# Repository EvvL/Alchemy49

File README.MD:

<p align="center">
   
  <br>
  
</p>

**Status:** Ordering final prototype

## Introduction

The Alchemy49 is a replacement pcb for the Magicforce 49 supporting south facing Switches, LEDs, PCB mounted stabilizers
and QMK. It's built around the SparkFun Pro Micro and designed to be easy to put together and solder using only one
surface mount component.

## BOM (Bill of Materials)

- 1x Promicro (or Compatible)
- 1x Micro USB Cable
- 1x XM7D-0512 MiniB (LCSC: C46398)
- 1x 6mm THT SPST Button
- 49x 1N4148 (LCSC: C14538)

If using LEDs:

- 49x 330 1/6w (LCSC: C119858)
- 49x 1.8mm LED (LCSC: C268275)
- 1x AO3402 (LCSC: C351406)
- 1x 100 1/6w (LCSC: C119846)
- 1x 10k 1/6w (LCSC: C119894)

## Layout

Layout Render by [KLE-Render](http://kle-render.herokuapp.com/)

Click [this link](http://www.keyboard-layout-editor.com/#/gists/9abd5a1e1122fe68672f75864f8e92a3) for the KLE layout

## Firmware

For now QMK is currently supported via [KBFirmware.com](https://kbfirmware.com/). Just upload the included
[Configuration/kbfirmware.json](https://github.com/EvvL/Alchemy49/raw/master/Configuration/kbfirmware.json) into
the site, tweak the layout to your liking and compile. The resulting hex file should be flashable using
[AVRDUDESS](https://github.com/zkemble/AVRDUDESS) or [AVRDUDE](http://www.nongnu.org/avrdude/).

If you don't want to adjust anything you can use the [included prebuilt hex file](https://github.com/EvvL/Alchemy49/raw/master/Configuration/alchemy49.hex)
with all the same configuration as the stock MagicForce49 layout.

## Renders

PCB Renders by [Tracespace](https://tracespace.io/view/)

## Copyright and Licensing

This project is licensed under the [Acheron Open-Source Hardware License V1.2](https://github.com/EvvL/Alchemy49/blob/master/LICENSE.md)

OSHWA Certification: [US000215](https://certification.oshwa.org/us000215.html)

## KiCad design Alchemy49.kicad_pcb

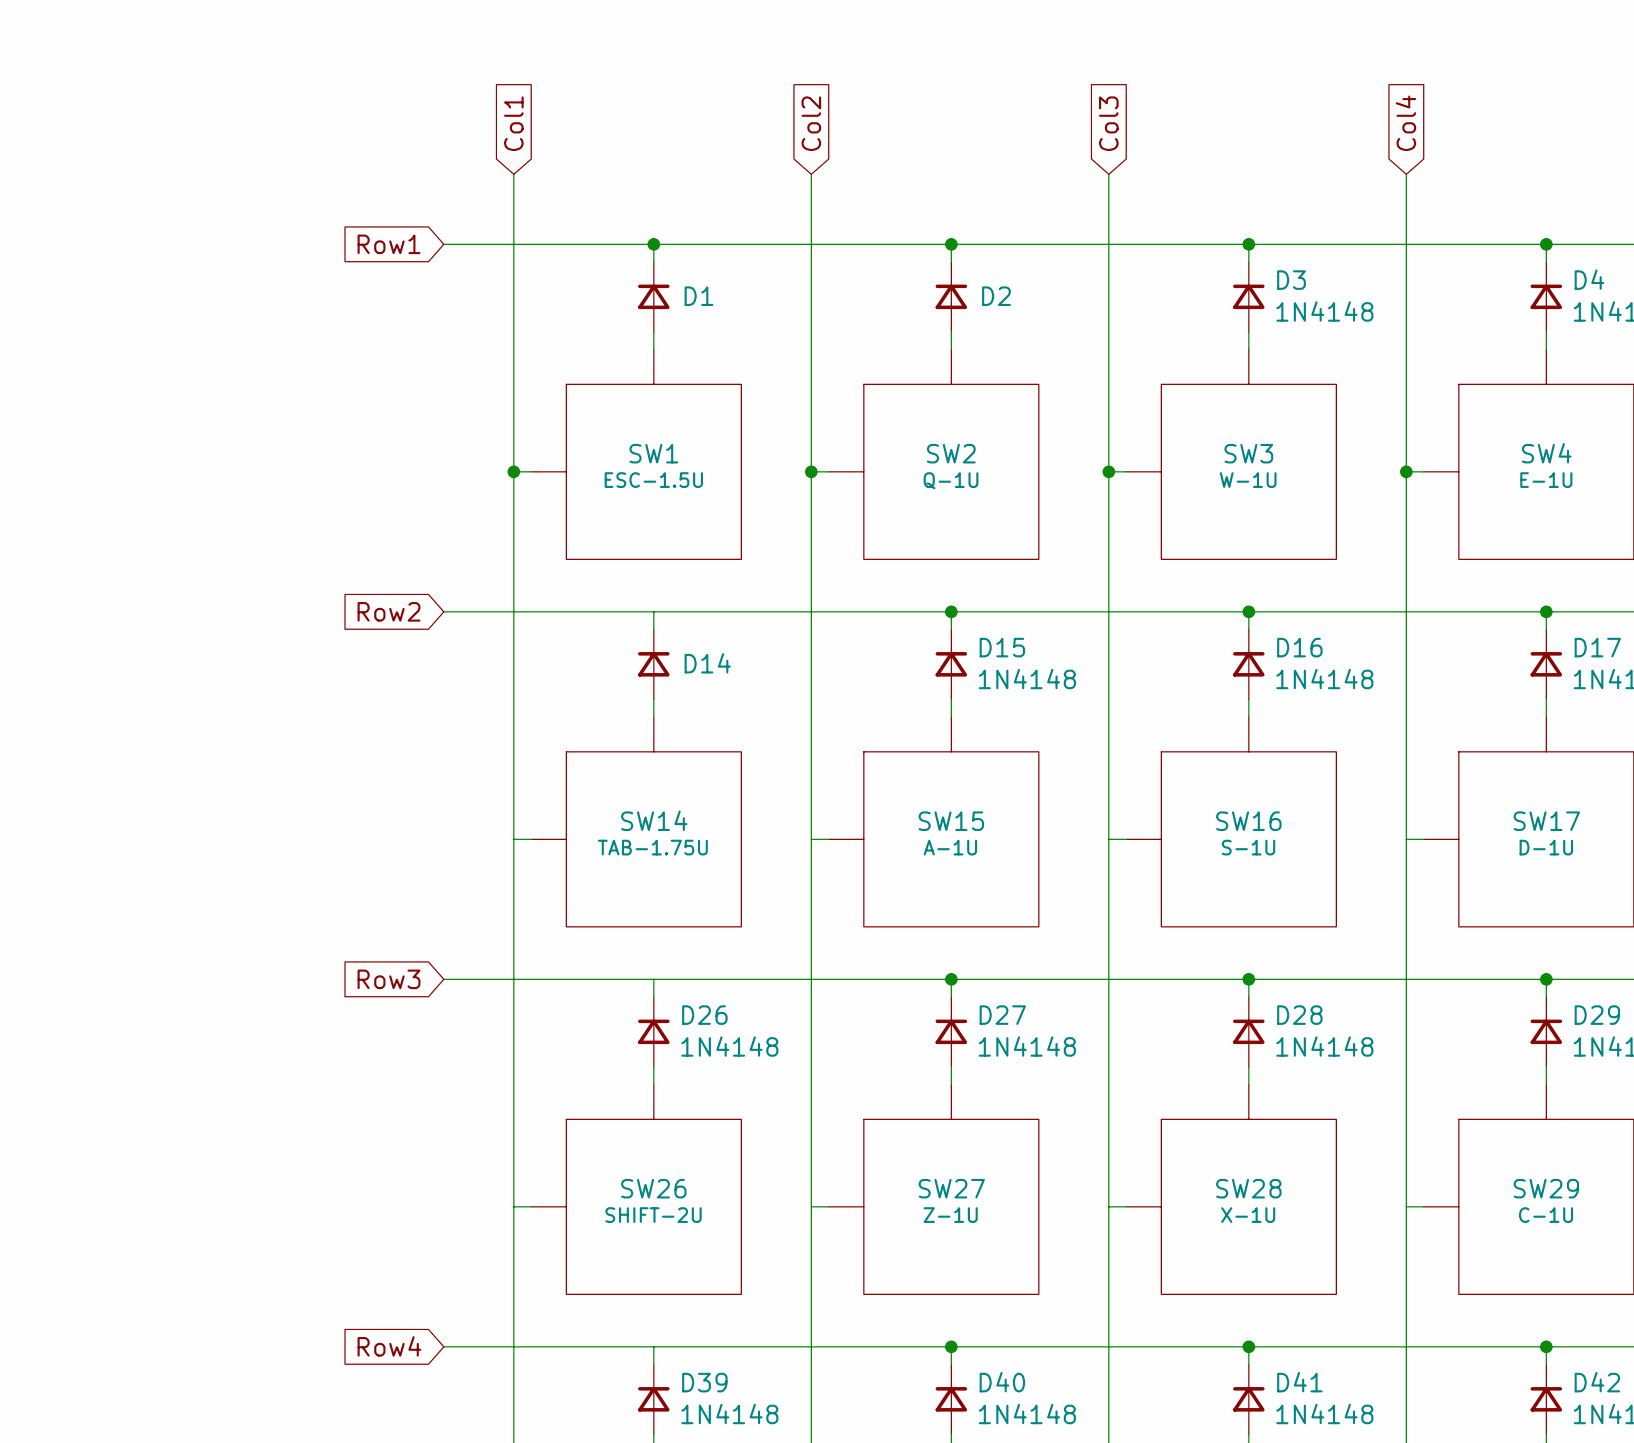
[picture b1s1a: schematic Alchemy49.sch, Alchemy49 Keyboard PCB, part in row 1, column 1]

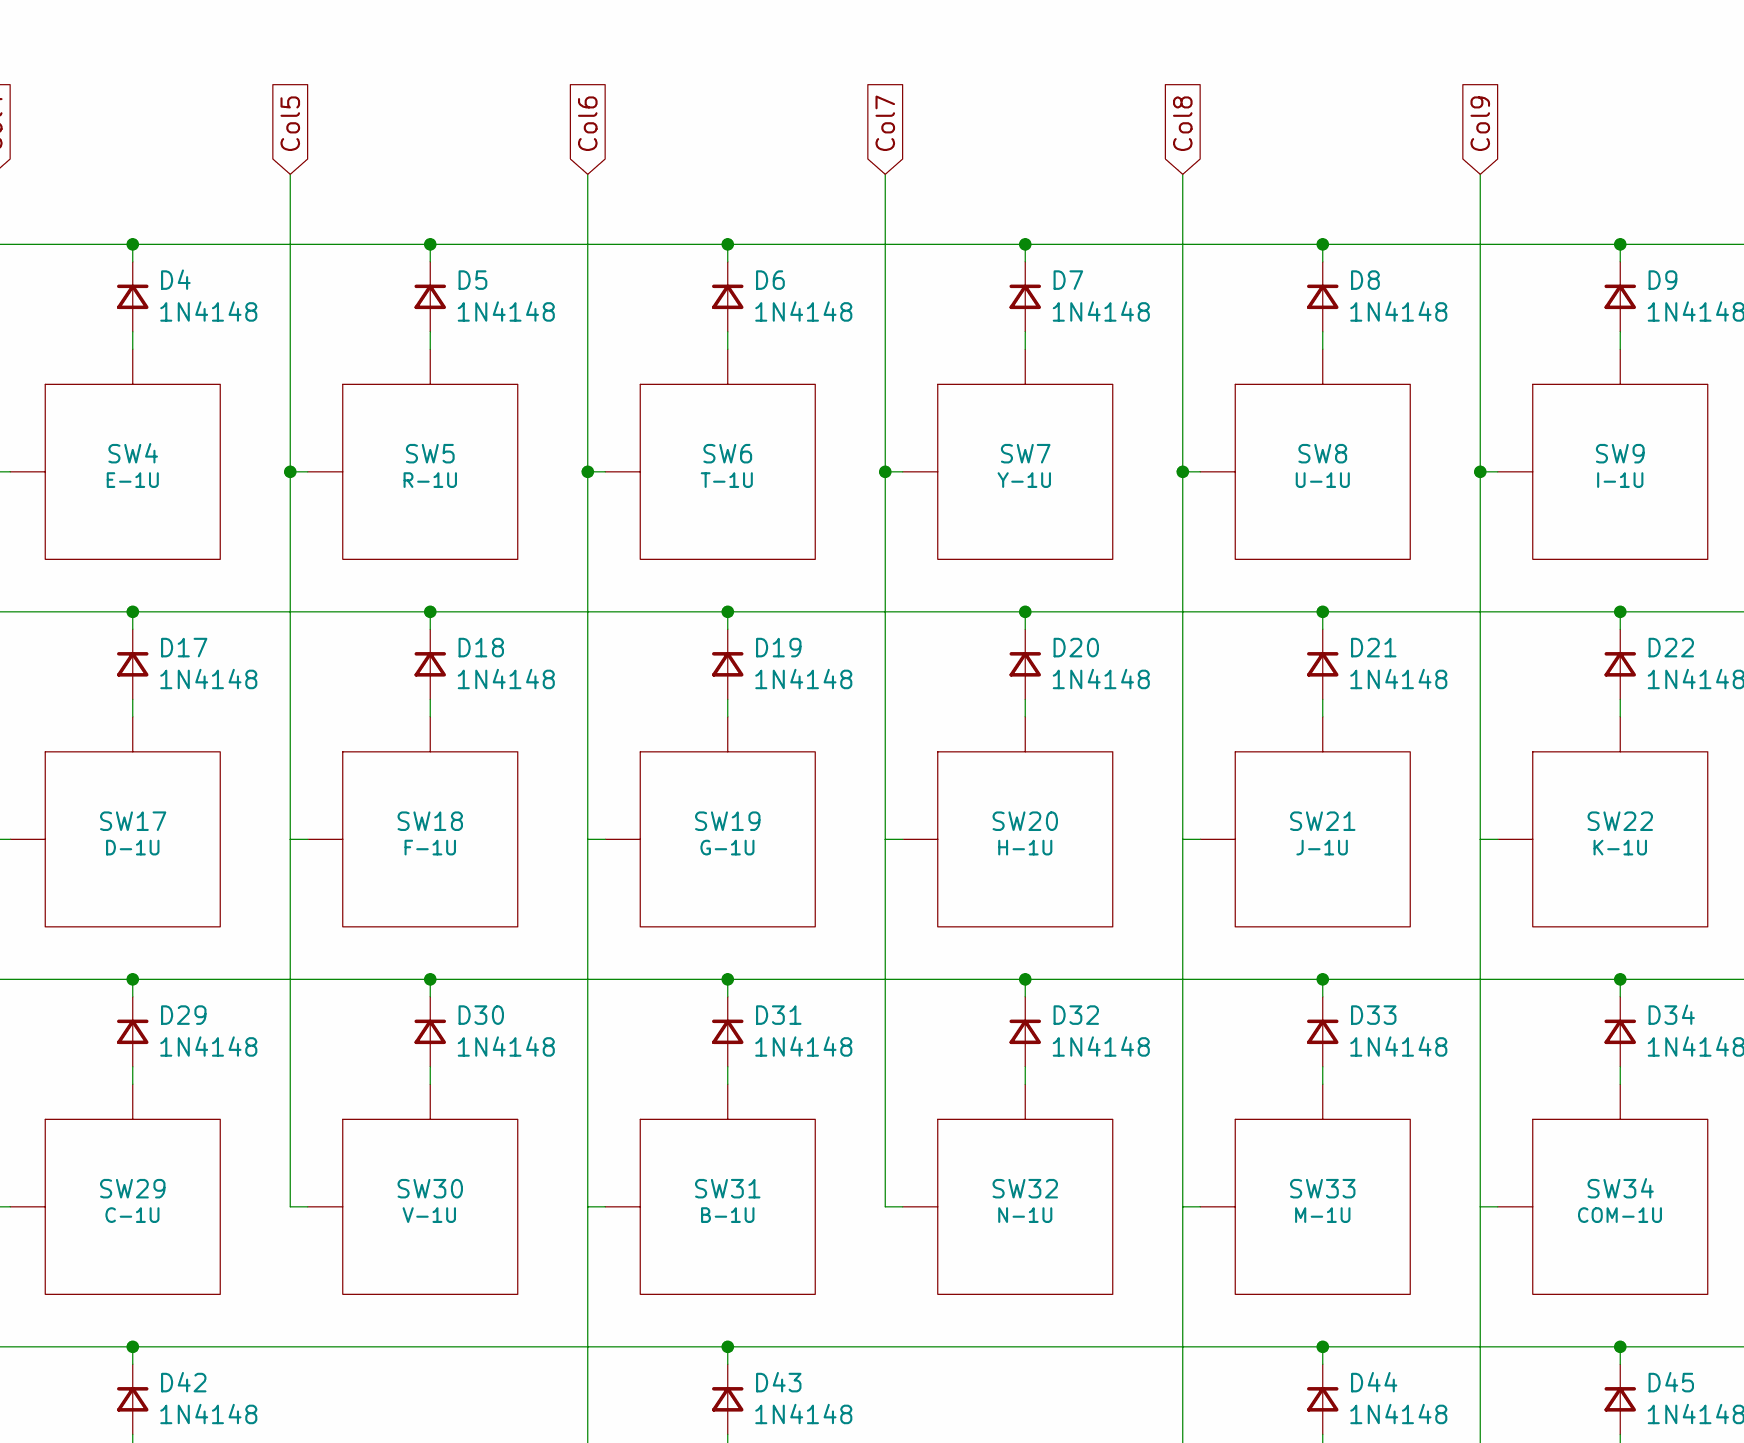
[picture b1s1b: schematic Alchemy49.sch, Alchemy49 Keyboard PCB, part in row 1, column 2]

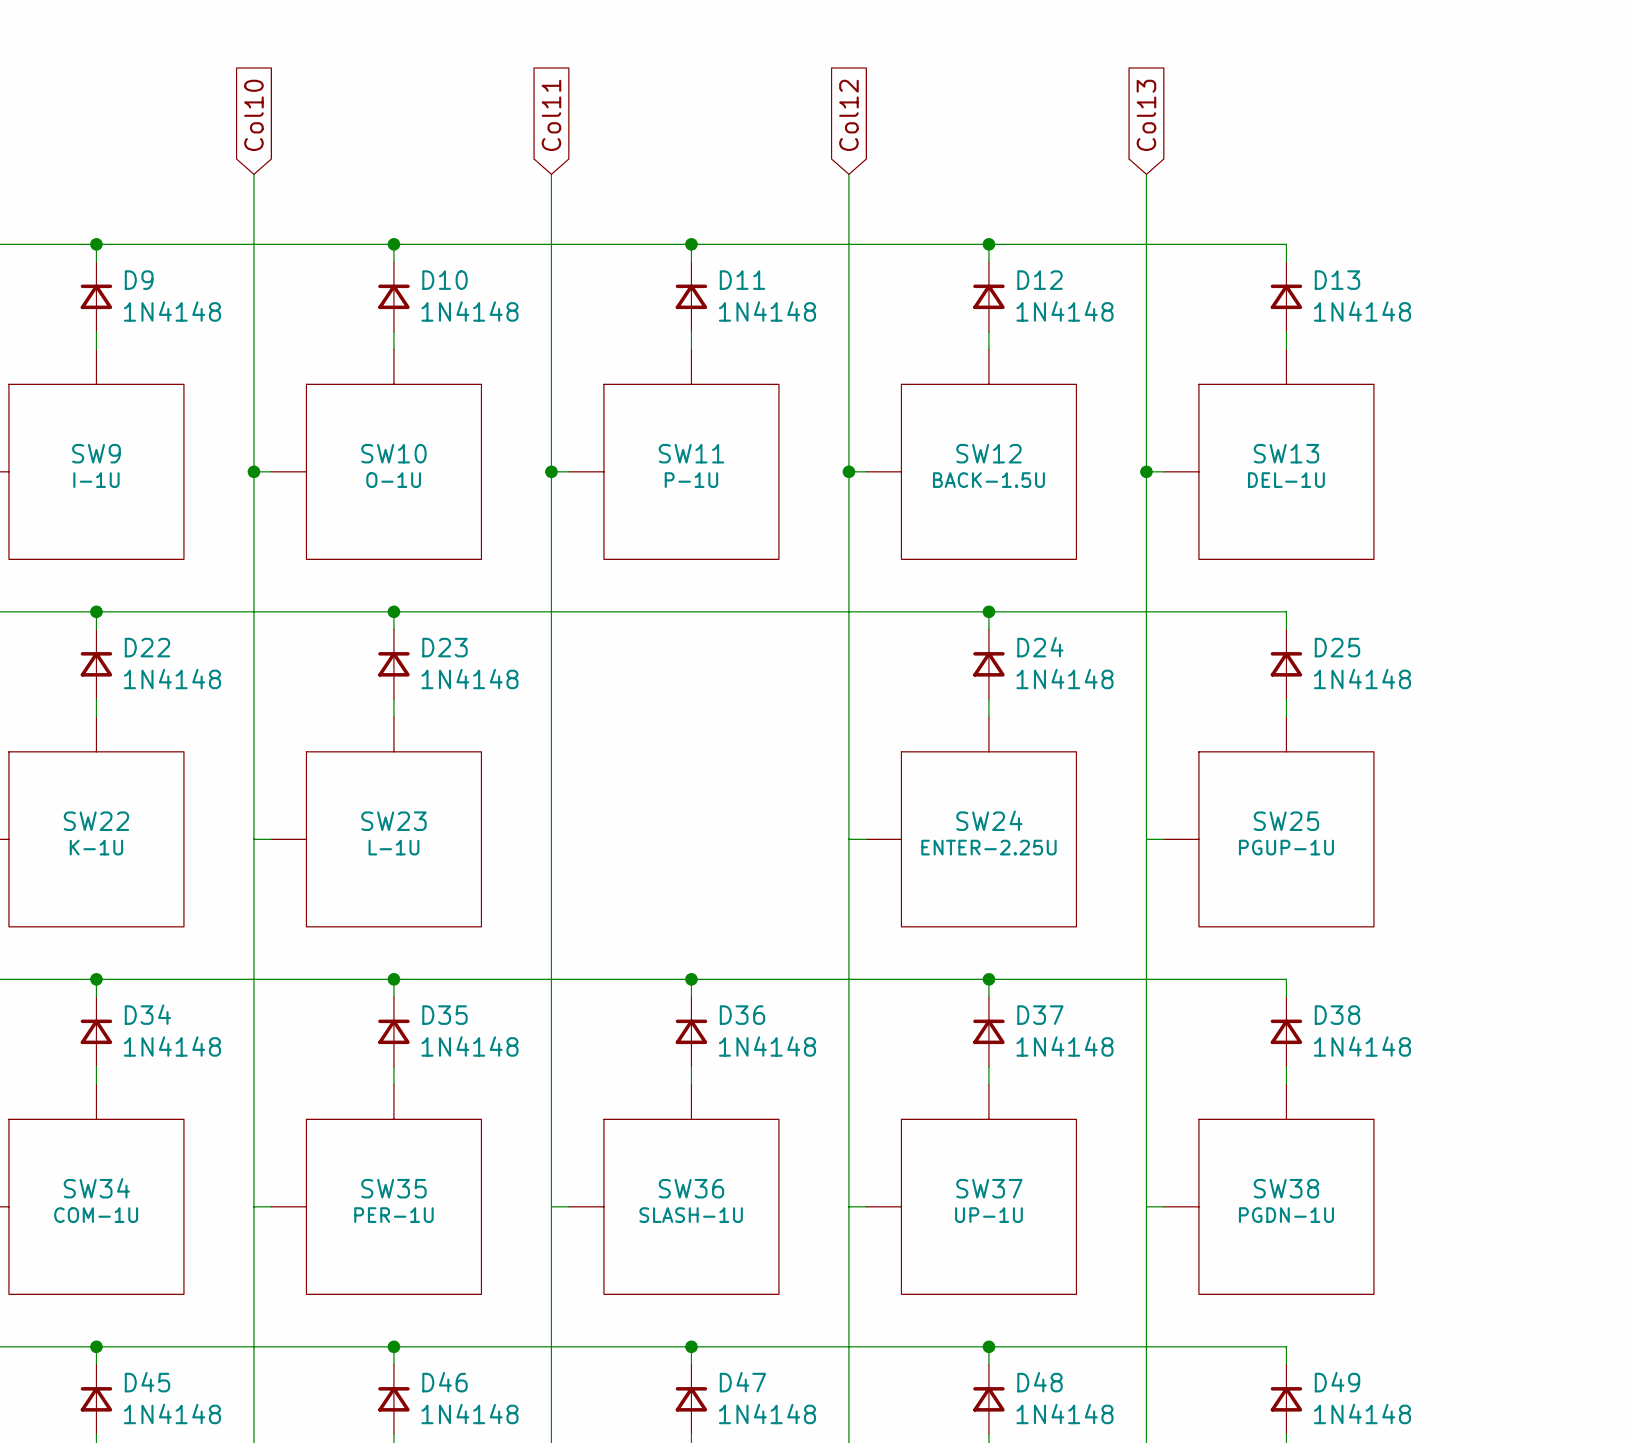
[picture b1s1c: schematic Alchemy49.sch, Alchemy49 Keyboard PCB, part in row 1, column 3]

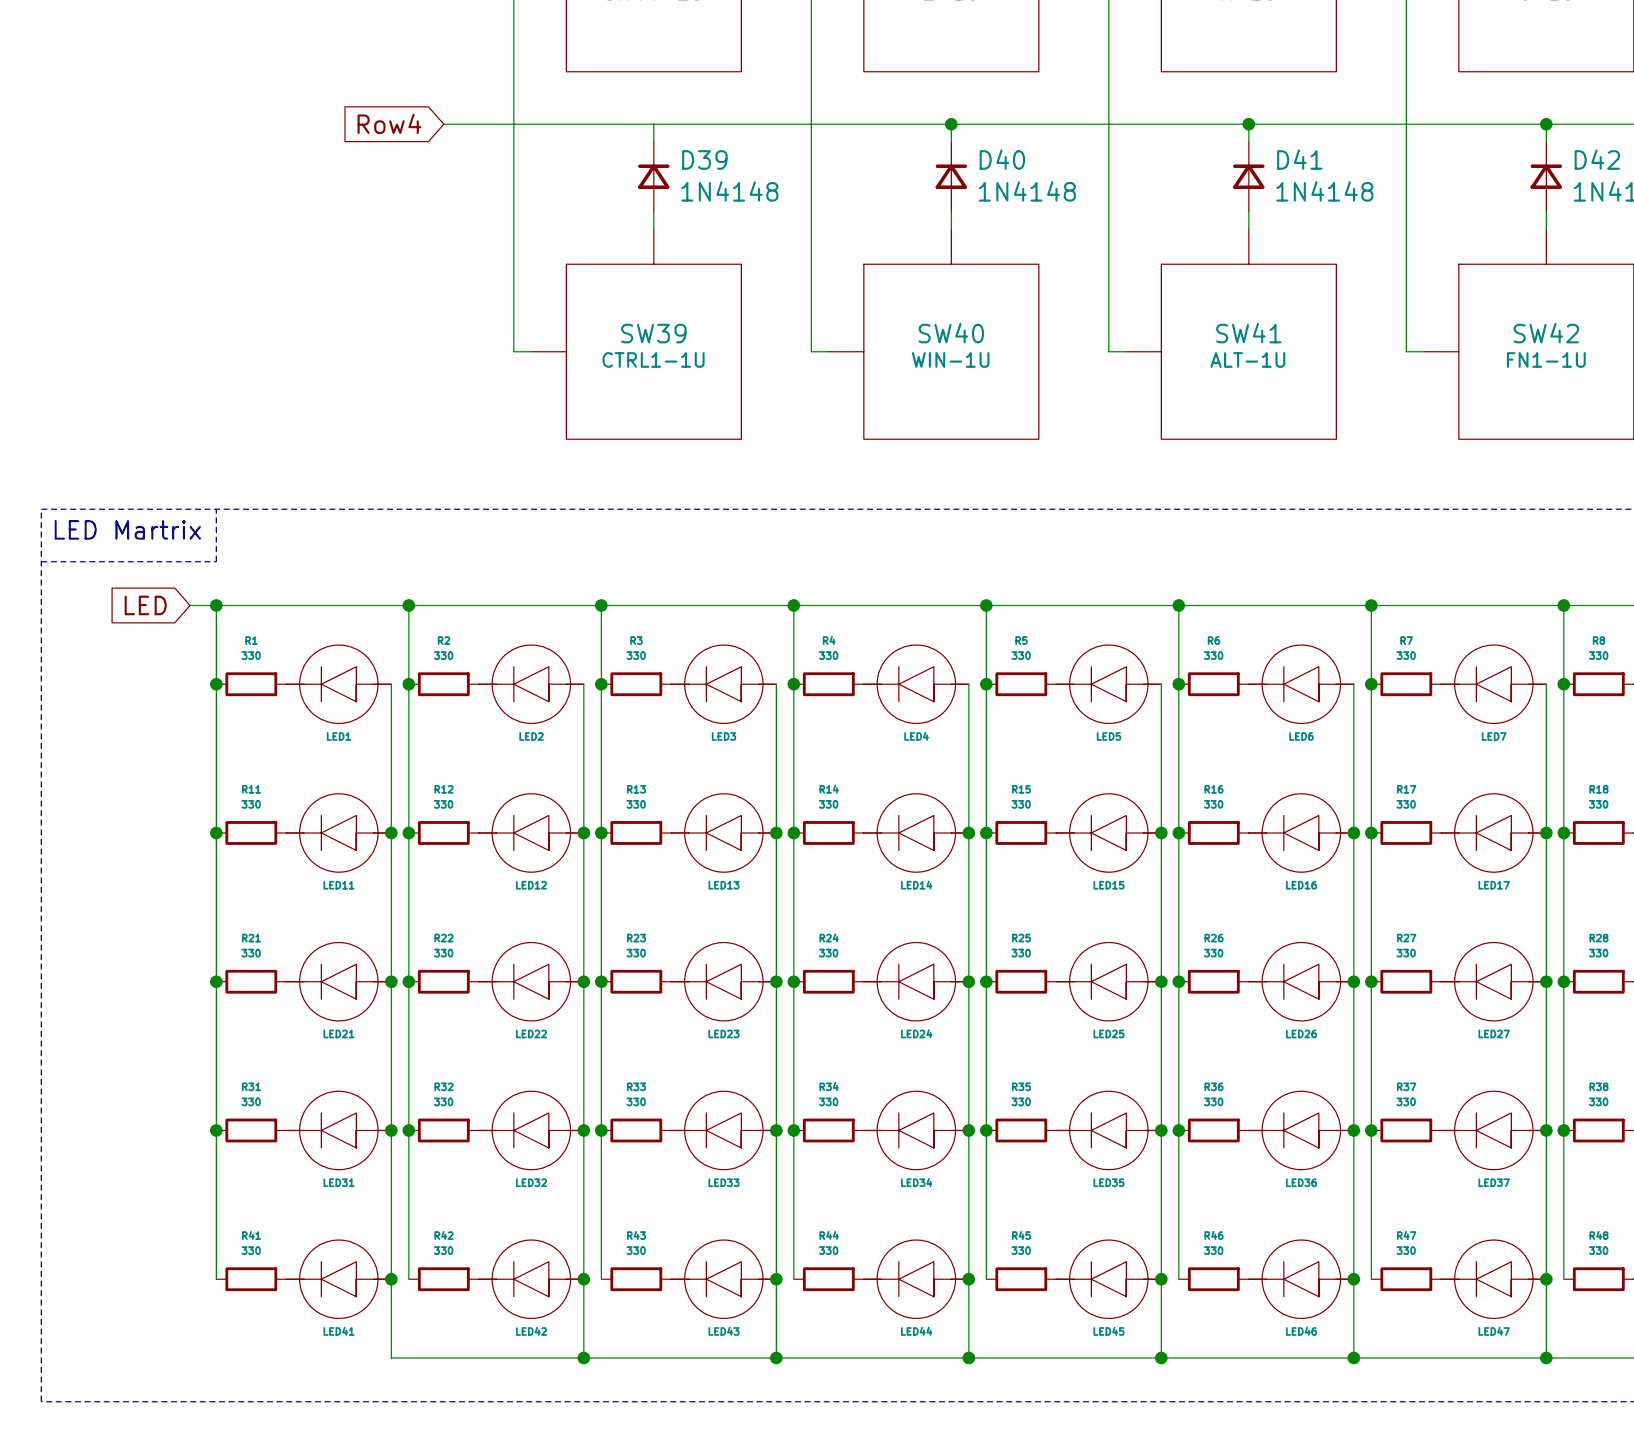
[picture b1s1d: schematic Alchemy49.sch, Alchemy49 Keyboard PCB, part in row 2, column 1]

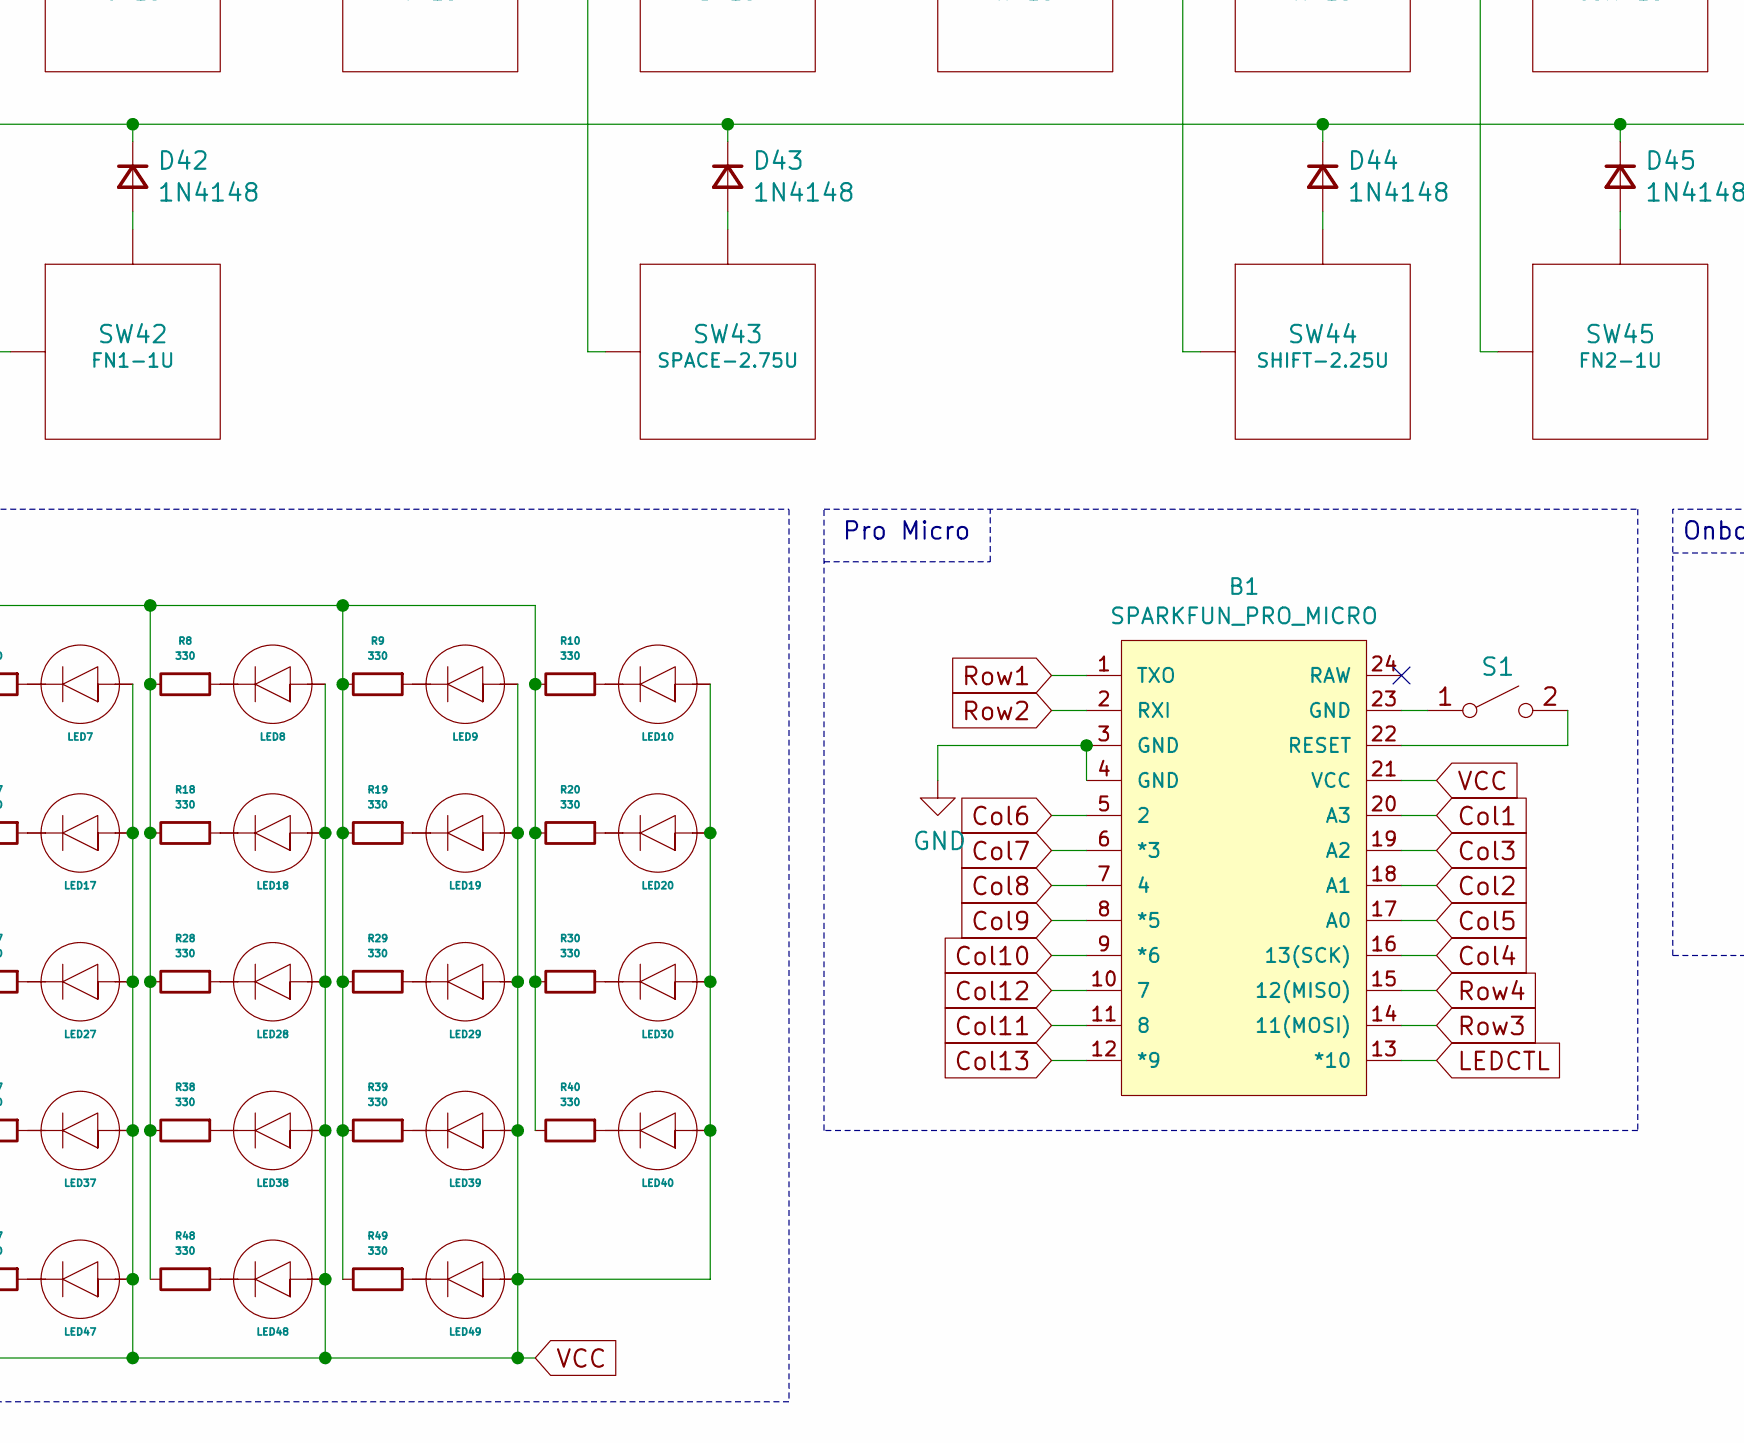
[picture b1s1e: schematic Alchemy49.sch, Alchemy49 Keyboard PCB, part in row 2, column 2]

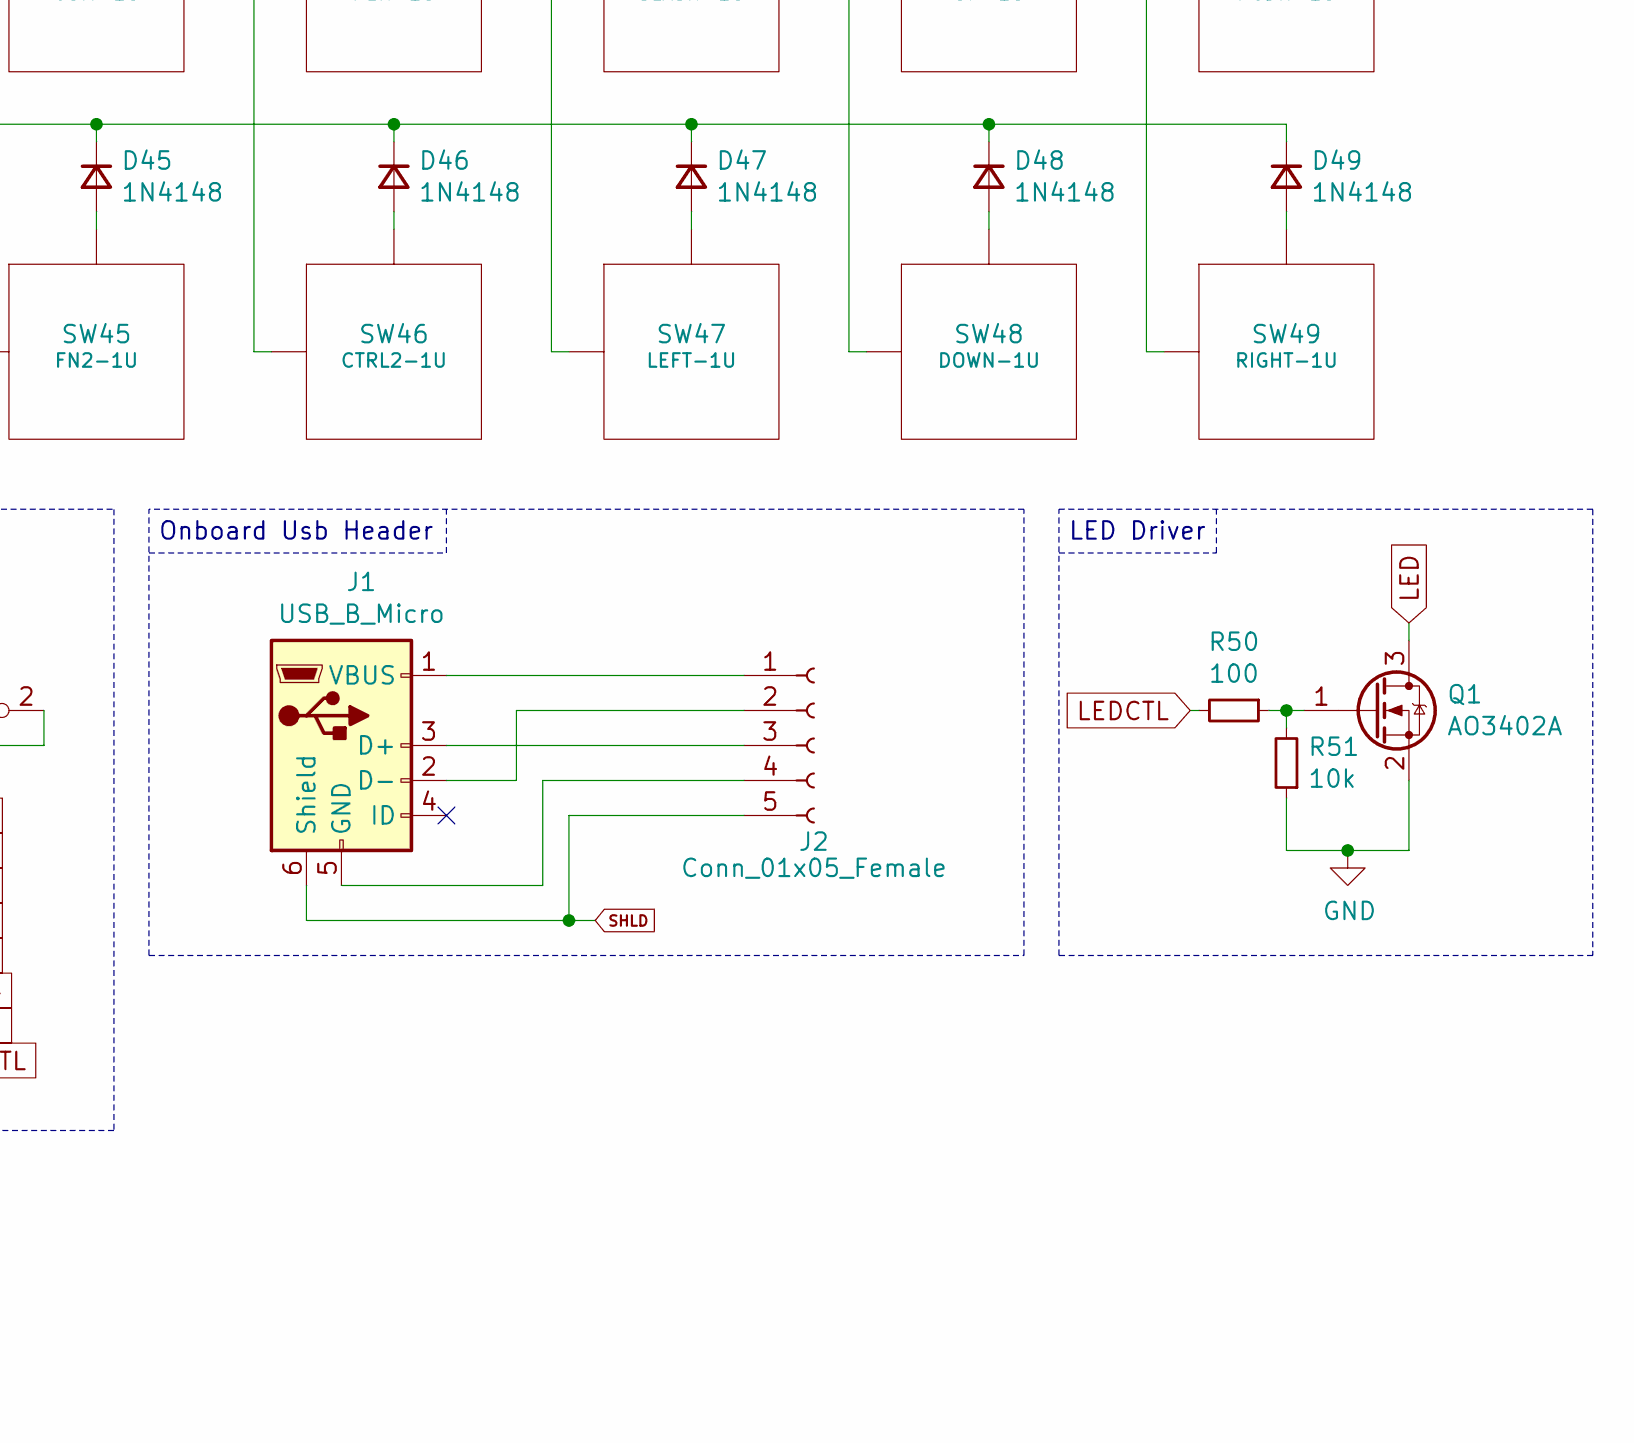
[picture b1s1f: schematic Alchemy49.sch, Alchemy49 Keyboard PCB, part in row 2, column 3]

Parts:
B1: SPARKFUN_PRO_MICRO
D1, D2, D3, D4, D5, D6, D7, D8, D9, D10, D11, D12, D13, D14, D15, D16, D17, D18, D19, D20, D21, D22, D23, D24, D25, D26, D27, D28, D29, D30, D31, D32, D33, D34, D35, D36, D37, D38, D39, D40, D41, D42, D43, D44, D45, D46, D47, D48, D49: 1N4148; D_THT_7.62mm_SOD-123; LCSC C14538
J1: USB_B_Micro; USB_MiniB_XM7D-0512; LCSC C46398
J2: Conn_01x05_Female; PinHeader_1x5_P2.54mm_Vertical
LED1, LED2, LED3, LED4, LED5, LED6, LED7, LED8, LED9, LED10, LED11, LED12, LED13, LED14, LED15, LED16, LED17, LED18, LED19, LED20, LED21, LED22, LED23, LED24, LED25, LED26, LED27, LED28, LED29, LED30, LED31, LED32, LED33, LED34, LED35, LED36, LED37, LED38, LED39, LED40, LED41, LED42, LED43, LED44, LED45, LED46, LED47, LED48, LED49: LED; LED_THT_2.54mm; LCSC C268275
Q1: AO3402A; SOT-23; LCSC C351406
R1, R2, R3, R4, R5, R6, R7, R8, R9, R10, R11, R12, R13, R14, R15, R16, R17, R18, R19, R20, R21, R22, R23, R24, R25, R26, R27, R28, R29, R30, R31, R32, R33, R34, R35, R36, R37, R38, R39, R40, R41, R42, R43, R44, R45, R46, R47, R48, R49: 330; R_THT_5.08mm_SMD_1206; LCSC C119858
R50: 100; R_THT_5.08mm_SMD_1206; LCSC C119846
R51: 10k; R_THT_5.08mm_SMD_1206; LCSC C119894
S1: SW_SPST; SW_PUSH_6mm
SW1: ESC-1.5U; MX150
SW2: Q-1U; MX100
SW3: W-1U; MX100
SW4: E-1U; MX100
SW5: R-1U; MX100
SW6: T-1U; MX100
SW7: Y-1U; MX100
SW8: U-1U; MX100
SW9: I-1U; MX100
SW10: O-1U; MX100
SW11: P-1U; MX100
SW12: BACK-1.5U; MX150
SW13: DEL-1U; MX100
SW14: TAB-1.75U; MX175
SW15: A-1U; MX100
SW16: S-1U; MX100
SW17: D-1U; MX100
SW18: F-1U; MX100
SW19: G-1U; MX100
SW20: H-1U; MX100
SW21: J-1U; MX100
SW22: K-1U; MX100
SW23: L-1U; MX100
SW24: ENTER-2.25U; MX225
SW25: PGUP-1U; MX100
SW26: SHIFT-2U; MX200
SW27: Z-1U; MX100
SW28: X-1U; MX100
SW29: C-1U; MX100
SW30: V-1U; MX100
SW31: B-1U; MX100
SW32: N-1U; MX100
SW33: M-1U; MX100
SW34: COM-1U; MX100
SW35: PER-1U; MX100
SW36: SLASH-1U; MX100
SW37: UP-1U; MX100
SW38: PGDN-1U; MX100
SW39: CTRL1-1U; MX100
SW40: WIN-1U; MX100
SW41: ALT-1U; MX100
SW42: FN1-1U; MX100
SW43: SPACE-2.75U; MX275R
SW44: SHIFT-2.25U; MX225R
SW45: FN2-1U; MX100
SW46: CTRL2-1U; MX100
SW47: LEFT-1U; MX100
SW48: DOWN-1U; MX100
SW49: RIGHT-1U; MX100

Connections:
Col1: B1.20 (A3), SW1.1 (Col), SW14.1 (Col), SW26.1 (Col), SW39.1 (Col)
Col2: B1.18 (A1), SW2.1 (Col), SW15.1 (Col), SW27.1 (Col), SW40.1 (Col)
Col3: B1.19 (A2), SW3.1 (Col), SW16.1 (Col), SW28.1 (Col), SW41.1 (Col)
Col4: B1.16 (13(SCK)), SW4.1 (Col), SW17.1 (Col), SW29.1 (Col), SW42.1 (Col)
Col5: B1.17 (A0), SW5.1 (Col), SW18.1 (Col), SW30.1 (Col)
Col6: B1.5 (2), SW6.1 (Col), SW19.1 (Col), SW31.1 (Col), SW43.1 (Col)
Col7: B1.6 (*3), SW7.1 (Col), SW20.1 (Col), SW32.1 (Col)
Col8: B1.7 (4), SW8.1 (Col), SW21.1 (Col), SW33.1 (Col), SW44.1 (Col)
Col9: B1.8 (*5), SW9.1 (Col), SW22.1 (Col), SW34.1 (Col), SW45.1 (Col)
Col10: B1.9 (*6), SW10.1 (Col), SW23.1 (Col), SW35.1 (Col), SW46.1 (Col)
Col11: B1.11 (8), SW11.1 (Col), SW36.1 (Col), SW47.1 (Col)
Col12: B1.10 (7), SW12.1 (Col), SW24.1 (Col), SW37.1 (Col), SW48.1 (Col)
Col13: B1.12 (*9), SW13.1 (Col), SW25.1 (Col), SW38.1 (Col), SW49.1 (Col)
GND: B1.3 (GND), B1.4 (GND), Q1.2 (S), R51.1
LED: Q1.3 (D), R1.2, R2.2, R3.2, R4.2, R5.2, R6.2, R7.2, R8.2, R9.2, R10.2, R11.2, R12.2, R13.2, R14.2, R15.2, R16.2, R17.2, R18.2, R19.2, R20.2, R21.2, R22.2, R23.2, R24.2, R25.2, R26.2, R27.2, R28.2, R29.2, R30.2, R31.2, R32.2, R33.2, R34.2, R35.2, R36.2, R37.2, R38.2, R39.2, R40.2, R41.2, R42.2, R43.2, R44.2, R45.2, R46.2, R47.2, R48.2, R49.2
LEDCTL: B1.13 (*10), R50.2
unnamed: B1.22 (RESET), S1.2 (B)
unnamed: B1.23 (GND), S1.1 (A)
unnamed: D1.2 (A), SW1.2 (Row)
unnamed: D2.2 (A), SW2.2 (Row)
unnamed: D3.2 (A), SW3.2 (Row)
unnamed: D4.2 (A), SW4.2 (Row)
unnamed: D5.2 (A), SW5.2 (Row)
unnamed: D6.2 (A), SW6.2 (Row)
unnamed: D7.2 (A), SW7.2 (Row)
unnamed: D8.2 (A), SW8.2 (Row)
unnamed: D9.2 (A), SW9.2 (Row)
unnamed: D10.2 (A), SW10.2 (Row)
unnamed: D11.2 (A), SW11.2 (Row)
unnamed: D12.2 (A), SW12.2 (Row)
unnamed: D13.2 (A), SW13.2 (Row)
unnamed: D14.2 (A), SW14.2 (Row)
unnamed: D15.2 (A), SW15.2 (Row)
unnamed: D16.2 (A), SW16.2 (Row)
unnamed: D17.2 (A), SW17.2 (Row)
unnamed: D18.2 (A), SW18.2 (Row)
unnamed: D19.2 (A), SW19.2 (Row)
unnamed: D20.2 (A), SW20.2 (Row)
unnamed: D21.2 (A), SW21.2 (Row)
unnamed: D22.2 (A), SW22.2 (Row)
unnamed: D23.2 (A), SW23.2 (Row)
unnamed: D24.2 (A), SW24.2 (Row)
unnamed: D25.2 (A), SW25.2 (Row)
unnamed: D26.2 (A), SW26.2 (Row)
unnamed: D27.2 (A), SW27.2 (Row)
unnamed: D28.2 (A), SW28.2 (Row)
unnamed: D29.2 (A), SW29.2 (Row)
unnamed: D30.2 (A), SW30.2 (Row)
unnamed: D31.2 (A), SW31.2 (Row)
unnamed: D32.2 (A), SW32.2 (Row)
unnamed: D33.2 (A), SW33.2 (Row)
unnamed: D34.2 (A), SW34.2 (Row)
unnamed: D35.2 (A), SW35.2 (Row)
unnamed: D36.2 (A), SW36.2 (Row)
unnamed: D37.2 (A), SW37.2 (Row)
unnamed: D38.2 (A), SW38.2 (Row)
unnamed: D39.2 (A), SW39.2 (Row)
unnamed: D40.2 (A), SW40.2 (Row)
unnamed: D41.2 (A), SW41.2 (Row)
unnamed: D42.2 (A), SW42.2 (Row)
unnamed: D43.2 (A), SW43.2 (Row)
unnamed: D44.2 (A), SW44.2 (Row)
unnamed: D45.2 (A), SW45.2 (Row)
unnamed: D46.2 (A), SW46.2 (Row)
unnamed: D47.2 (A), SW47.2 (Row)
unnamed: D48.2 (A), SW48.2 (Row)
unnamed: D49.2 (A), SW49.2 (Row)
unnamed: J1.1 (VBUS), J2.1
unnamed: J1.2 (D-), J2.2
unnamed: J1.3 (D+), J2.3
unnamed: J1.5 (GND), J2.4
unnamed: LED1.K, R1.1
unnamed: LED2.K, R2.1
unnamed: LED3.K, R3.1
unnamed: LED4.K, R4.1
unnamed: LED5.K, R5.1
unnamed: LED6.K, R6.1
unnamed: LED7.K, R7.1
unnamed: LED8.K, R8.1
unnamed: LED9.K, R9.1
unnamed: LED10.K, R10.1
unnamed: LED11.K, R11.1
unnamed: LED12.K, R12.1
unnamed: LED13.K, R13.1
unnamed: LED14.K, R14.1
unnamed: LED15.K, R15.1
unnamed: LED16.K, R16.1
unnamed: LED17.K, R17.1
unnamed: LED18.K, R18.1
unnamed: LED19.K, R19.1
unnamed: LED20.K, R20.1
unnamed: LED21.K, R21.1
unnamed: LED22.K, R22.1
unnamed: LED23.K, R23.1
unnamed: LED24.K, R24.1
unnamed: LED25.K, R25.1
unnamed: LED26.K, R26.1
unnamed: LED27.K, R27.1
unnamed: LED28.K, R28.1
unnamed: LED29.K, R29.1
unnamed: LED30.K, R30.1
unnamed: LED31.K, R31.1
unnamed: LED32.K, R32.1
unnamed: LED33.K, R33.1
unnamed: LED34.K, R34.1
unnamed: LED35.K, R35.1
unnamed: LED36.K, R36.1
unnamed: LED37.K, R37.1
unnamed: LED38.K, R38.1
unnamed: LED39.K, R39.1
unnamed: LED40.K, R40.1
unnamed: LED41.K, R41.1
unnamed: LED42.K, R42.1
unnamed: LED43.K, R43.1
unnamed: LED44.K, R44.1
unnamed: LED45.K, R45.1
unnamed: LED46.K, R46.1
unnamed: LED47.K, R47.1
unnamed: LED48.K, R48.1
unnamed: LED49.K, R49.1
unnamed: Q1.1 (G), R50.1, R51.2
Row1: B1.1 (TXO), D1.1 (K), D2.1 (K), D3.1 (K), D4.1 (K), D5.1 (K), D6.1 (K), D7.1 (K), D8.1 (K), D9.1 (K), D10.1 (K), D11.1 (K), D12.1 (K), D13.1 (K)
Row2: B1.2 (RXI), D14.1 (K), D15.1 (K), D16.1 (K), D17.1 (K), D18.1 (K), D19.1 (K), D20.1 (K), D21.1 (K), D22.1 (K), D23.1 (K), D24.1 (K), D25.1 (K)
Row3: B1.14 (11(MOSI)), D26.1 (K), D27.1 (K), D28.1 (K), D29.1 (K), D30.1 (K), D31.1 (K), D32.1 (K), D33.1 (K), D34.1 (K), D35.1 (K), D36.1 (K), D37.1 (K), D38.1 (K)
Row4: B1.15 (12(MISO)), D39.1 (K), D40.1 (K), D41.1 (K), D42.1 (K), D43.1 (K), D44.1 (K), D45.1 (K), D46.1 (K), D47.1 (K), D48.1 (K), D49.1 (K)
SHLD: J1.6 (Shield), J2.5
VCC: B1.21 (VCC), LED1.A, LED2.A, LED3.A, LED4.A, LED5.A, LED6.A, LED7.A, LED8.A, LED9.A, LED10.A, LED11.A, LED12.A, LED13.A, LED14.A, LED15.A, LED16.A, LED17.A, LED18.A, LED19.A, LED20.A, LED21.A, LED22.A, LED23.A, LED24.A, LED25.A, LED26.A, LED27.A, LED28.A, LED29.A, LED30.A, LED31.A, LED32.A, LED33.A, LED34.A, LED35.A, LED36.A, LED37.A, LED38.A, LED39.A, LED40.A, LED41.A, LED42.A, LED43.A, LED44.A, LED45.A, LED46.A, LED47.A, LED48.A, LED49.A

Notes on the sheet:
Onboard Usb Header
Pro Micro
LED Martrix
LED Driver

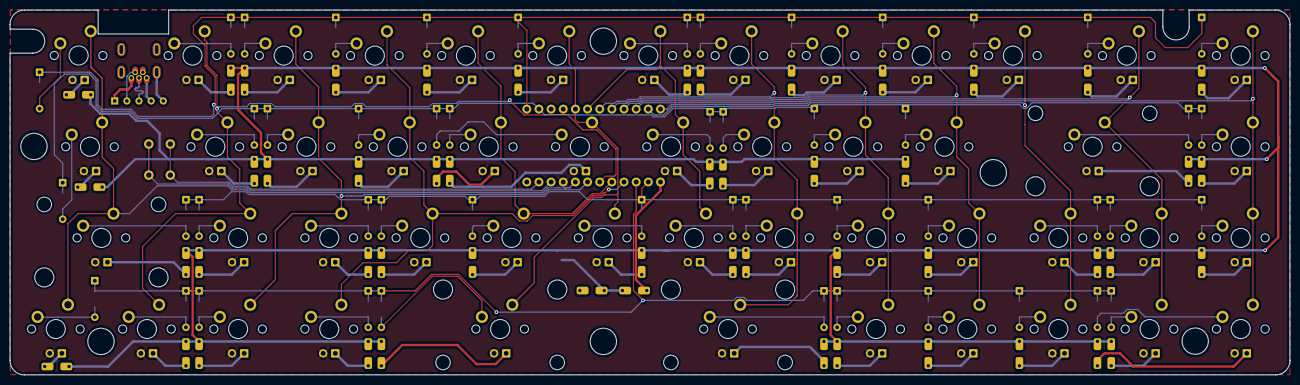
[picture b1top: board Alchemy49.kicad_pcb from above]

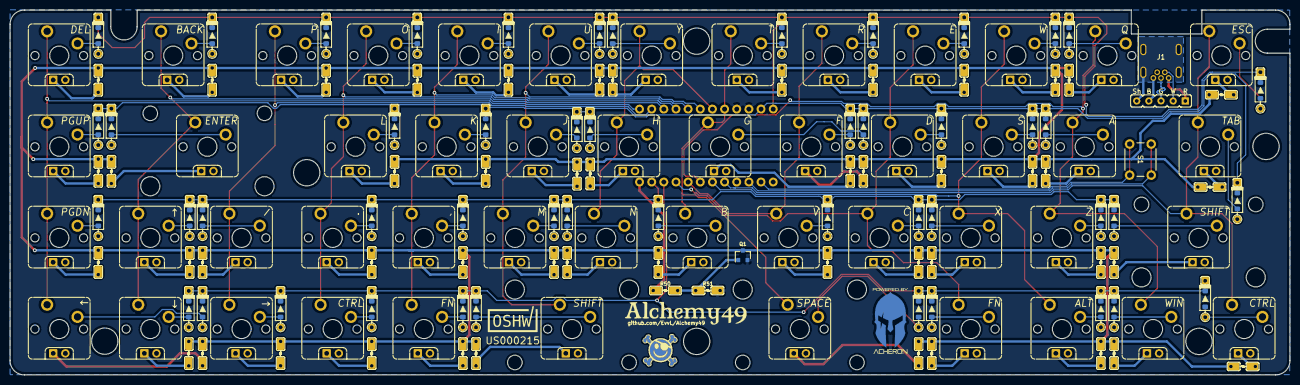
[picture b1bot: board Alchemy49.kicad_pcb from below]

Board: 2 copper layers, 267.5 x 76.2 mm, 253 parts (204 on the bottom side), 127 nets.

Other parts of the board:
,: Switch SilkS
.: Switch SilkS
/: Switch SilkS
A: Switch SilkS
ALT: Switch SilkS
B: Switch SilkS
BACK: Switch SilkS
C: Switch SilkS
CTRL: Switch SilkS
CTRL#2: Switch SilkS
D: Switch SilkS
DEL: Switch SilkS
E: Switch SilkS
ENTER: Switch SilkS
ESC: Switch SilkS
F: Switch SilkS
FN: Switch SilkS
FN#2: Switch SilkS
G: Switch SilkS
H: Switch SilkS
I: Switch SilkS
J: Switch SilkS
K: Switch SilkS
L: Switch SilkS
M: Switch SilkS
N: Switch SilkS
O: Switch SilkS
OSHW_Mono_0.25_Scale: US000215; OSHW_Mono_0.25_Scale
P: Switch SilkS
PGDN: Switch SilkS
PGUP: Switch SilkS
Q: Switch SilkS
R: Switch SilkS
S: Switch SilkS
SHIFT: Switch SilkS
SHIFT#2: Switch SilkS
SPACE: Switch SilkS
T: Switch SilkS
TAB: Switch SilkS
U: Switch SilkS
V: Switch SilkS
W: Switch SilkS
WIN: Switch SilkS
X: Switch SilkS
Y: Switch SilkS
Z: Switch SilkS
←: Switch SilkS
↑: Switch SilkS
→: Switch SilkS
↓: Switch SilkS

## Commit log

2019-11-25 Inital Release
2019-11-25 Rerouted the USB data lines
2019-11-27 Updated to new XM7D footprint in the Acheron Library
2019-11-27 Updated Acheron Library
2019-12-11 Added Switch Silkscreen Outlines
2019-12-11 Adjusted MOSFET location
2019-12-13 Added Bottom Silk Screen
2020-01-02 Finalized Board Design
2020-01-04 Updated led traces
2020-01-06 Prototypes Ordered
2020-01-12 First set of minor size adjustments
    Updated some of the edge cuts for a better fit, updated the board renders to match what the prototypes are
2020-01-21 Prototype Adjustments
    * Added working KBFirmware config and hex files.
    * Added example AVRDUDESS screenshot
    * Added datasheet and part numbers to sch
    * Adjusted pcb outlin and holes
2020-01-25 Cut layer adjustments for final
2020-01-27 OSHWA Certification
2020-01-27 EvvL Logo
2020-02-20 Changed MOSFET to FDS6630A
2020-03-16 flipped the leds around the correct way
2020-05-26 Changed MOSFET to AO3402, Removed 3D models from display
2020-07-14 New Graphics
    Added newest gerbers and graphics. Also added LCSC field to sch
2020-11-03 Changed to combination THT and surfacemount for the diodes
2020-11-04 Added new combined THT and 1206 footprint for the resistors
2020-11-05 reworked new footprint and fixed issues
